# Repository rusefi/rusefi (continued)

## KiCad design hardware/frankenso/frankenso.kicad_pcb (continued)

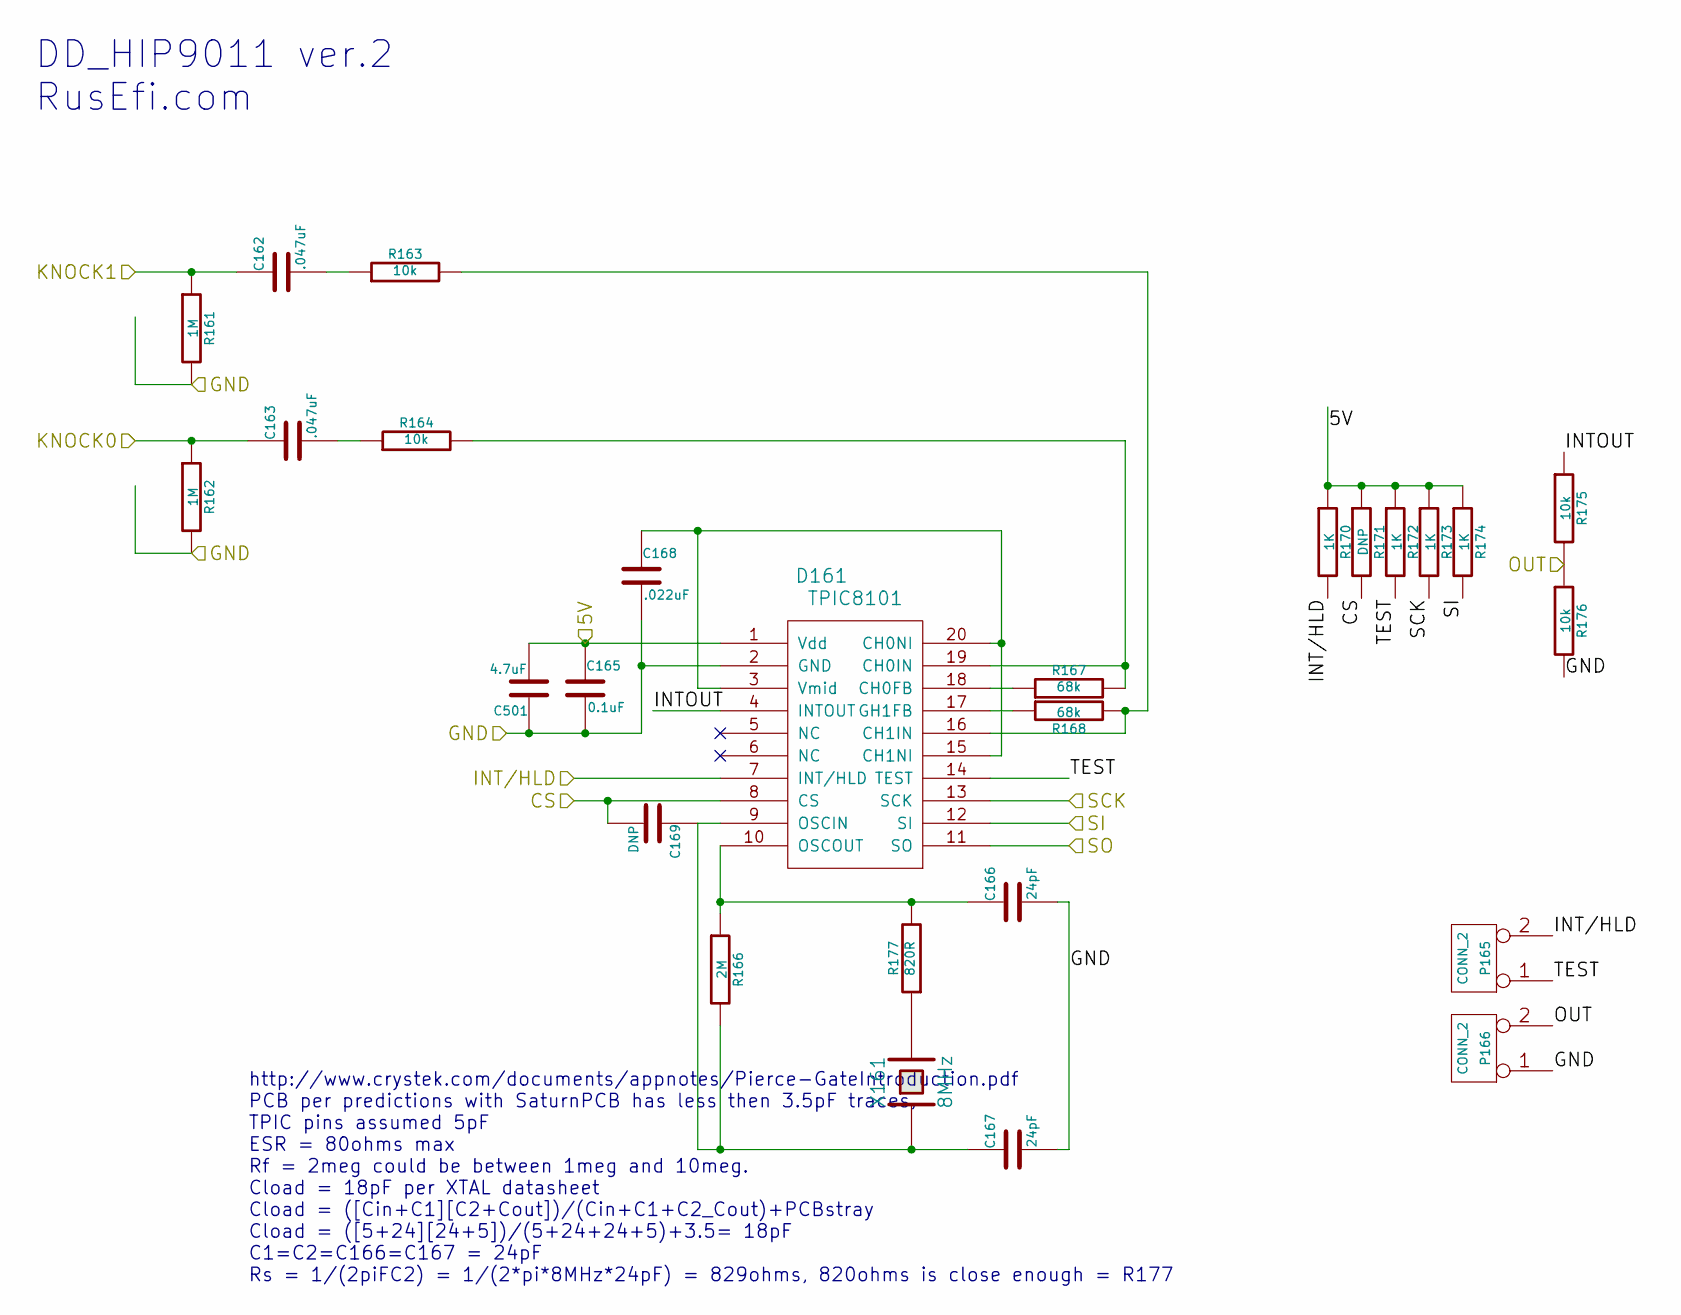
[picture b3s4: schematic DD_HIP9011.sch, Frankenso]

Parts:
C162, C163: .047uF; SM0805
C165: 0.1uF; SM0805
C166, C167: 24pF; SM0805
C168: .022uF; SM0805
C169: DNP; SM0805
C501: 4.7uF; SM0805
D161: TPIC8101; SO20L
P165, P166: CONN_2; PIN_ARRAY_2X1
R161, R162: 1M; SM0805
R163, R164, R175, R176: 10k; SM0805
R166: 2M; SM0805
R167, R168: 68k; SM0805
R170, R172, R173, R174: 1K; SM0805
R171: DNP; SM0805
R177: 820R; SM0805
X161: 8MHz; Q_49U3HMS

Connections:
/DD_HIP9011/5V: C165.1, C501.2, D161.1 (Vdd), R170.1, R171.1, R172.1, R173.1, R174.1; also elsewhere on the board
/DD_HIP9011/CS: C169.2, D161.8 (CS), R171.2; also elsewhere on the board
/DD_HIP9011/INT/HLD: D161.7 (INT/HLD), P165.2 (PM), R170.2; also elsewhere on the board
/DD_HIP9011/INTOUT: D161.4 (INTOUT), R175.1
/DD_HIP9011/KNOCK0: C163.1, R162.1; also elsewhere on the board
/DD_HIP9011/KNOCK1: C162.1, R161.1; also elsewhere on the board
/DD_HIP9011/OUT: P166.2 (PM), R175.2, R176.1; also elsewhere on the board
/DD_HIP9011/TEST: D161.14 (TEST), P165.1, R172.2
/stm32f407_board/PB13: D161.13 (SCK), R173.2; also elsewhere on the board
/stm32f407_board/PB14: D161.11 (SO); also elsewhere on the board
/stm32f407_board/PB15: D161.12 (SI), R174.2; also elsewhere on the board
GND: C165.2, C166.2, C167.2, C168.2, C501.1, D161.2 (GND), P166.1, R161.2, R162.2, R176.2; also elsewhere on the board
unnamed: C168.1, D161.3 (Vmid), D161.15 (CH1NI), D161.20 (CH0NI)
unnamed: C167.1, C169.1, D161.9 (OSCIN), R166.2, X161.1
unnamed: R177.1, X161.2
unnamed: C162.2, R163.1
unnamed: C166.1, D161.10 (OSCOUT), R166.1, R177.2
unnamed: C163.2, R164.1
unnamed: D161.17 (GH1FB), R168.1
unnamed: D161.19 (CH0IN), R164.2, R167.2
unnamed: D161.16 (CH1IN), R163.2, R168.2
unnamed: D161.18 (CH0FB), R167.1

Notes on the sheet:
DD_HIP9011 ver.2 RusEfi.com
http://www.crystek.com/documents/appnotes/Pierce-GateIntroduction.pdf PCB per predictions with SaturnPCB has less then 3.5pF traces, TPIC pins assumed 5pF ESR = 80ohms max Rf = 2meg could be between 1meg and 10meg. Cload = 18pF per XTAL datasheet Cload = ([Cin+C1][C2+Cout])/(Cin+C1+C2_Cout)+PCBstra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

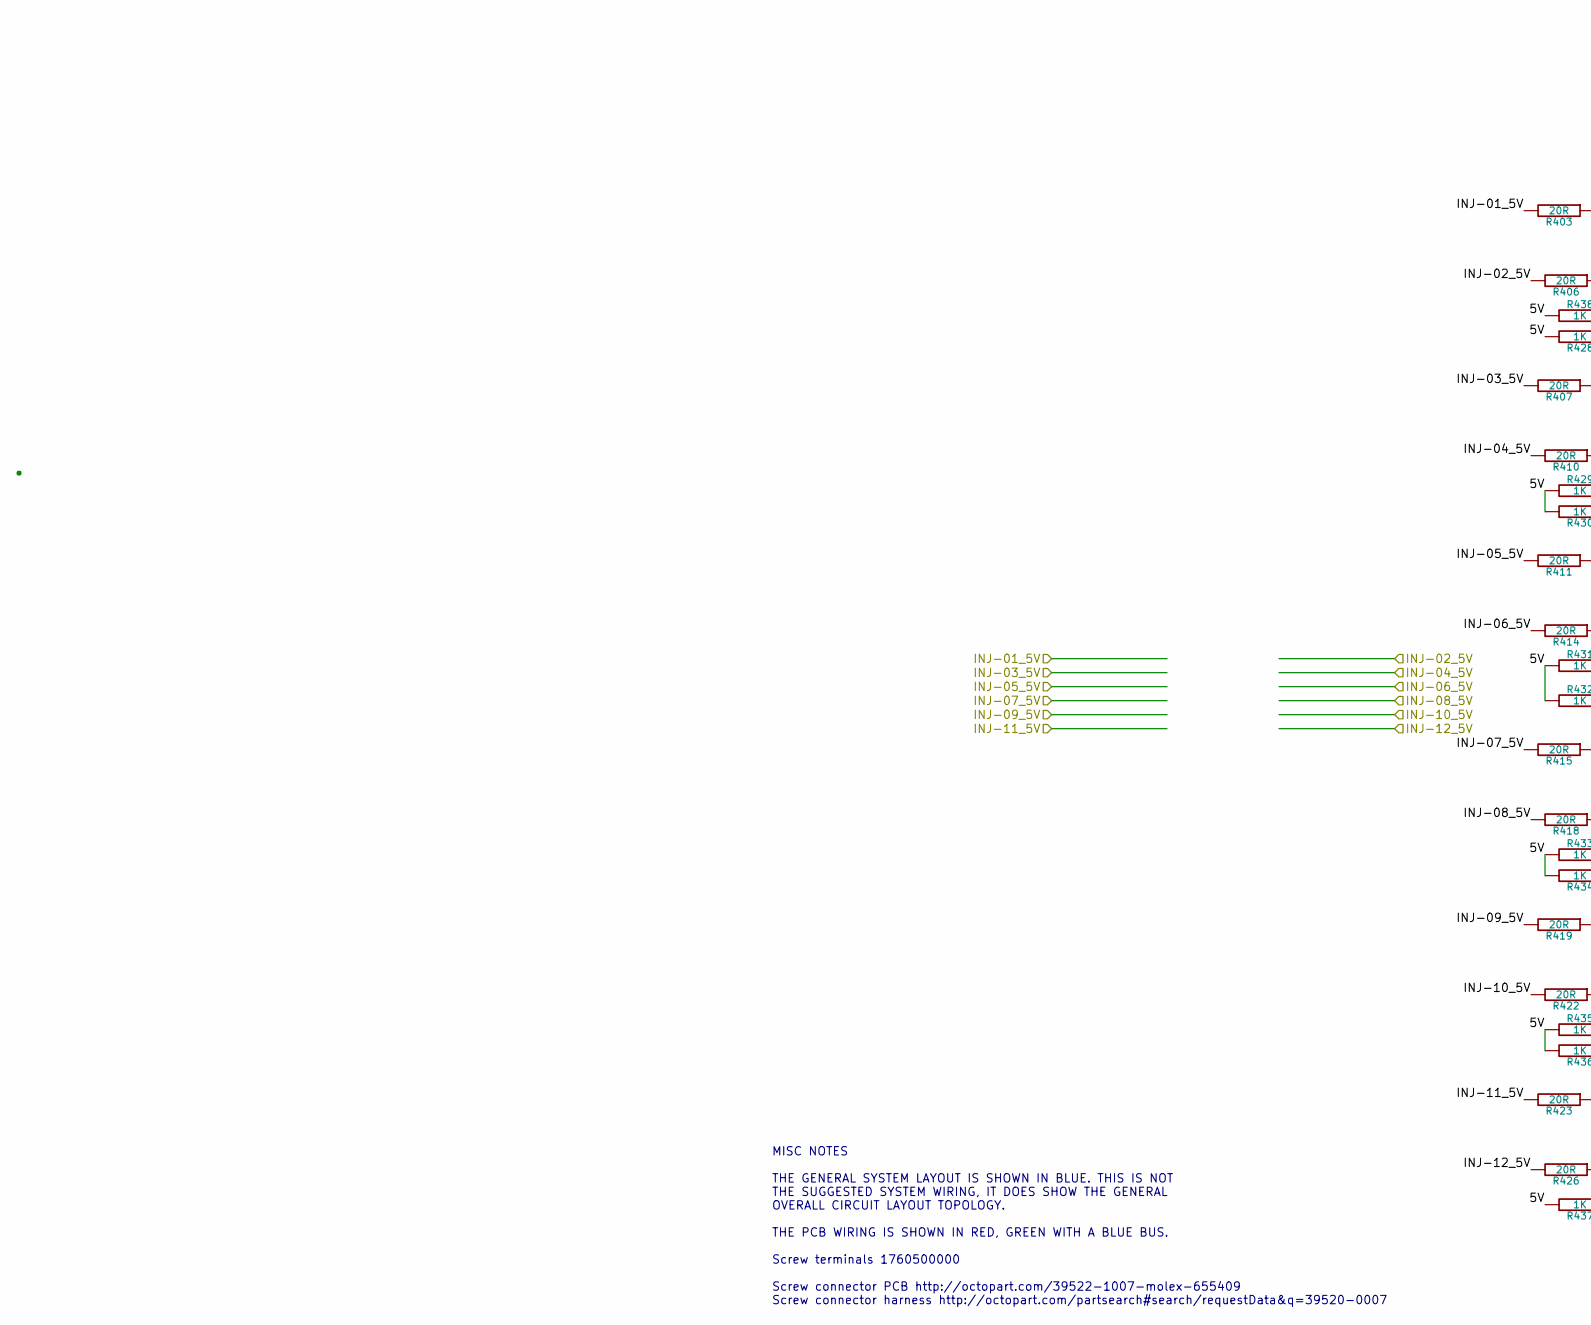
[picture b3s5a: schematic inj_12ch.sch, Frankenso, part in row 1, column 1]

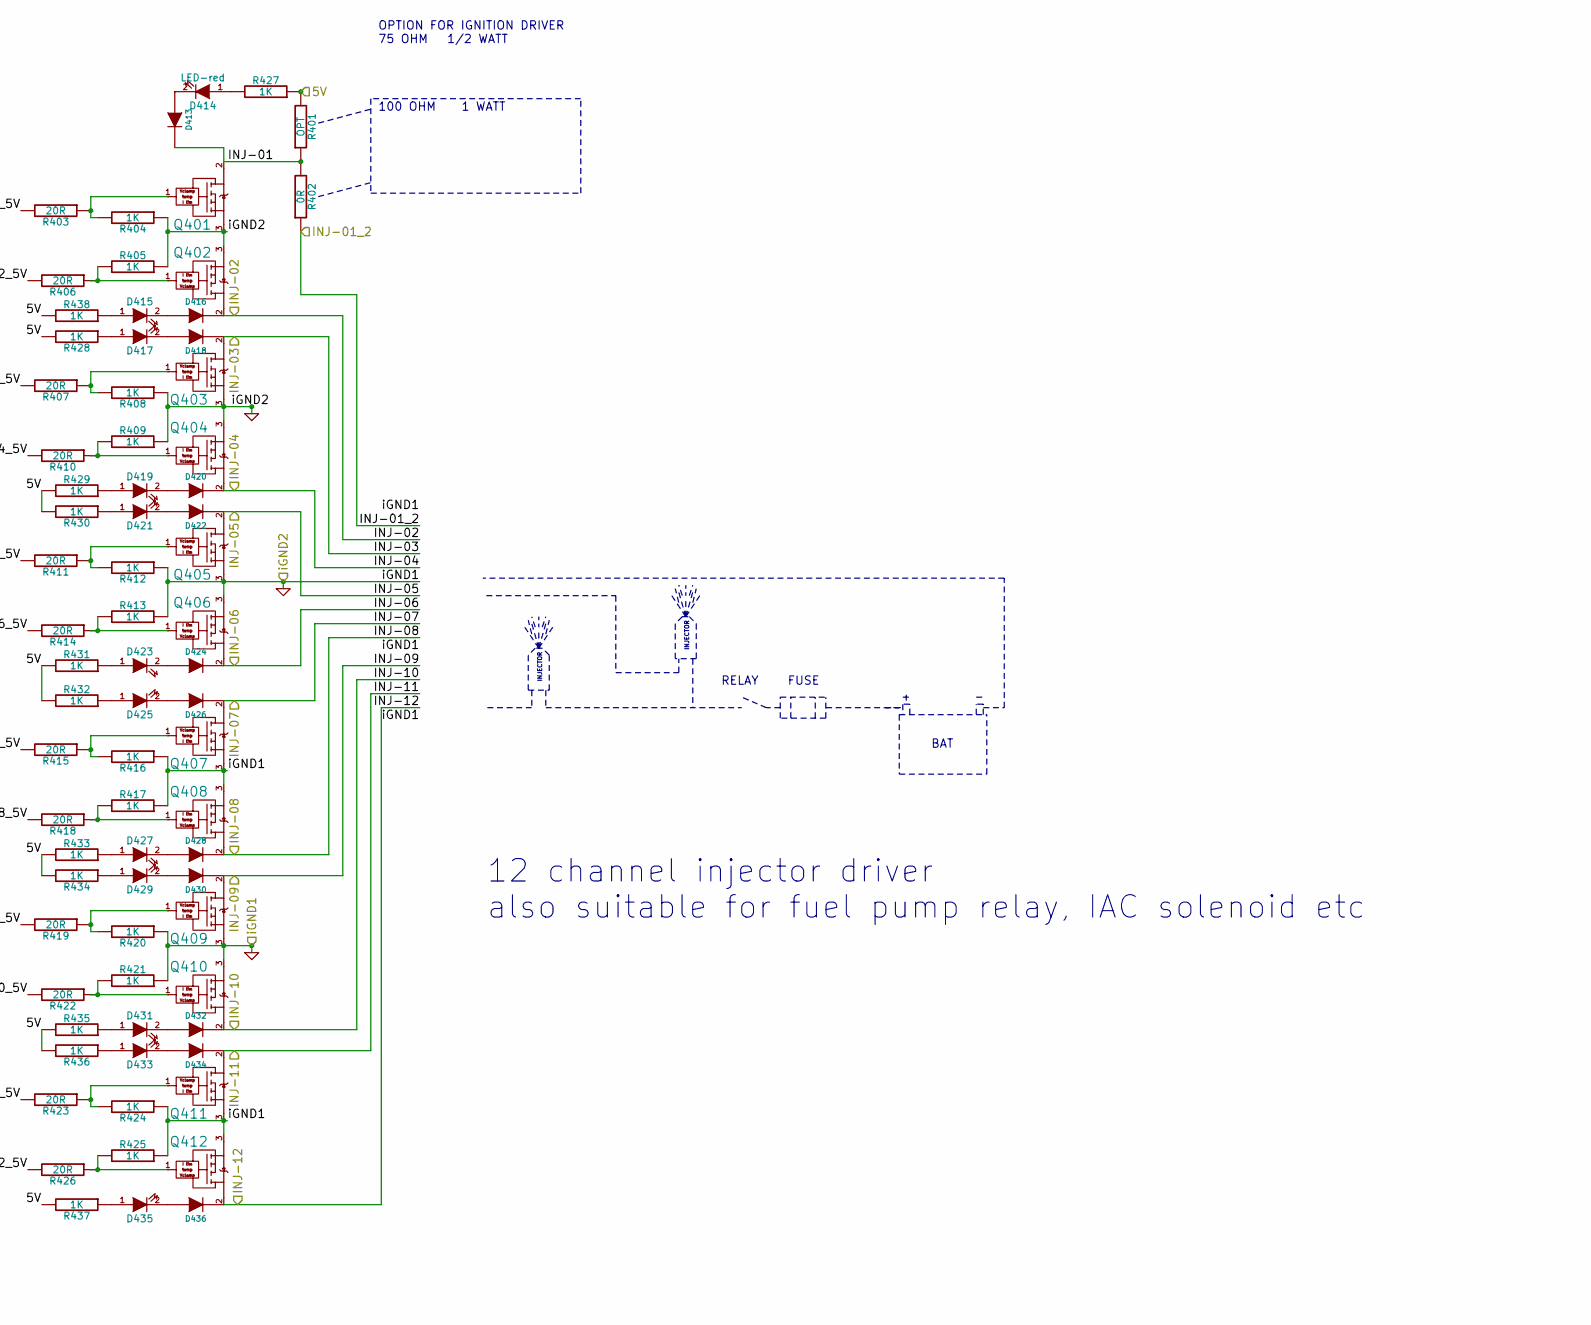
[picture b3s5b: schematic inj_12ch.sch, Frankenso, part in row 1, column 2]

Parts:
D413, D416, D418, D420, D422, D424, D426, D428, D430, D432, D434, D436: DIODE; SOD-123
D414, D415, D417, D419, D421, D423, D425, D427, D429, D431, D433, D435: LED-red; LED-0805_A
Q401, Q402, Q403, Q404, Q405, Q406, Q407, Q408, Q409, Q410, Q411, Q412: OVP_DRIVER; SO8E_ST
R401: OPT; SIL-2
R402: 0R; SIL-2
R403, R406, R407, R410, R411, R414, R415, R418, R419, R422, R423, R426: 20R; SM0805
R404, R405, R408, R409, R412, R413, R416, R417, R420, R421, R424, R425, R427, R428, R429, R430, R431, R432, R433, R434, R435, R436, R437, R438: 1K; SM0805

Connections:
/DD_HIP9011/5V: R401.2, R427.1, R428.2, R429.2, R430.2, R431.2, R432.2, R433.2, R434.2, R435.2, R436.2, R437.2, R438.2; also elsewhere on the board
/inj_12ch/INJ-01: D413.2 (K), Q401.2 (C), R401.1, R402.2
/inj_12ch/INJ-01_2: R402.1; also elsewhere on the board
/inj_12ch/INJ-01_5V: R403.2; also elsewhere on the board
/inj_12ch/INJ-02: D416.2 (K), Q402.2 (C); also elsewhere on the board
/inj_12ch/INJ-02_5V: R406.2; also elsewhere on the board
/inj_12ch/INJ-03: D418.2 (K), Q403.2 (C); also elsewhere on the board
/inj_12ch/INJ-03_5V: R407.2; also elsewhere on the board
/inj_12ch/INJ-04: D420.2 (K), Q404.2 (C); also elsewhere on the board
/inj_12ch/INJ-04_5V: R410.2; also elsewhere on the board
/inj_12ch/INJ-05: D422.2 (K), Q405.2 (C); also elsewhere on the board
/inj_12ch/INJ-05_5V: R411.2; also elsewhere on the board
/inj_12ch/INJ-06: D424.2 (K), Q406.2 (C); also elsewhere on the board
/inj_12ch/INJ-06_5V: R414.2; also elsewhere on the board
/inj_12ch/INJ-07: D426.2 (K), Q407.2 (C); also elsewhere on the board
/inj_12ch/INJ-07_5V: R415.2; also elsewhere on the board
/inj_12ch/INJ-08: D428.2 (K), Q408.2 (C); also elsewhere on the board
/inj_12ch/INJ-08_5V: R418.2; also elsewhere on the board
/inj_12ch/INJ-09: D430.2 (K), Q409.2 (C); also elsewhere on the board
/inj_12ch/INJ-09_5V: R419.2; also elsewhere on the board
/inj_12ch/INJ-10: D432.2 (K), Q410.2 (C); also elsewhere on the board
/inj_12ch/INJ-10_5V: R422.2; also elsewhere on the board
/inj_12ch/INJ-11: D434.2 (K), Q411.2 (C); also elsewhere on the board
/inj_12ch/INJ-11_5V: R423.2; also elsewhere on the board
/inj_12ch/INJ-12: D436.2 (K), Q412.2 (C); also elsewhere on the board
/inj_12ch/INJ-12_5V: R426.2; also elsewhere on the board
GND: Q401.3 (E), Q402.3 (E), Q403.3 (E), Q404.3 (E), Q405.3 (E), Q406.3 (E), Q407.3 (E), Q408.3 (E), Q409.3 (E), Q410.3 (E), Q411.3 (E), Q412.3 (E), R404.1, R405.1, R408.1, R409.1, R412.1, R413.1, R416.1, R417.1, R420.1, R421.1, R424.1, R425.1; also elsewhere on the board
unnamed: Q401.1 (G), R403.1, R404.2
unnamed: Q403.1 (G), R407.1, R408.2
unnamed: Q406.1 (G), R413.2, R414.1
unnamed: Q412.1 (G), R425.2, R426.1
unnamed: Q410.1 (G), R421.2, R422.1
unnamed: Q408.1 (G), R417.2, R418.1
unnamed: D413.1 (A), D414.2 (K)
unnamed: D414.1 (A), R427.2
unnamed: Q402.1 (G), R405.2, R406.1
unnamed: Q404.1 (G), R409.2, R410.1
unnamed: Q405.1 (G), R411.1, R412.2
unnamed: Q407.1 (G), R415.1, R416.2
unnamed: Q409.1 (G), R419.1, R420.2
unnamed: Q411.1 (G), R423.1, R424.2
unnamed: D417.1 (A), R428.1
unnamed: D417.2 (K), D418.1 (A)
unnamed: D419.2 (K), D420.1 (A)
unnamed: D419.1 (A), R429.1
unnamed: D421.2 (K), D422.1 (A)
unnamed: D421.1 (A), R430.1
unnamed: D423.2 (K), D424.1 (A)
unnamed: D423.1 (A), R431.1
unnamed: D415.2 (K), D416.1 (A)
unnamed: D415.1 (A), R438.1
unnamed: D433.1 (A), R436.1
unnamed: D431.2 (K), D432.1 (A)
unnamed: D431.1 (A), R435.1
unnamed: D433.2 (K), D434.1 (A)
unnamed: D435.2 (K), D436.1 (A)
unnamed: D435.1 (A), R437.1
unnamed: D427.1 (A), R433.1
unnamed: D425.2 (K), D426.1 (A)
unnamed: D425.1 (A), R432.1
unnamed: D427.2 (K), D428.1 (A)
unnamed: D429.2 (K), D430.1 (A)
unnamed: D429.1 (A), R434.1

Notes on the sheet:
INJECTOR
RELAY
MISC NOTES THE GENERAL SYSTEM LAYOUT IS SHOWN IN BLUE. THIS IS NOT THE SUGGESTED SYSTEM WIRING, IT DOES SHOW THE GENERAL OVERALL CIRCUIT LAYOUT TOPOLOGY. THE PCB WIRING IS SHOWN IN RED, GREEN WITH A BLUE BUS. Screw terminals 1760500000 Screw connector PCB http://octopart.com/39522-1007-molex-655409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
BAT
FUSE
OPTION FOR IGNITION DRIVER 75 OHM 1/2 WATT 100 OHM 1 WATT
12 channel injector driver also suitable for fuel pump relay, IAC solenoid etc

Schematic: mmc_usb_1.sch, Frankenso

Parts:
C351: 4700pF; SM0805
C352, C353: 47pF; SM0805
C354, C358: 4.7uF; SM0805
C355, C356, C357, C701, C702: 0.1uF; SM0805
D351, D701, D702: LED-grn; LED-0805_A
D703: DOUBLE_SCHOTTKY; sot23
FB701: FILTER; SM0805_jumper
J351: MINI-USB-5P-3400020P1
J352: MINI-USB-5P-3400020P1V; MINI-USB_RCTP_V-T_B
P352: MICRO-SDCARD-CONNECTOR-3300060P1
Q701: MOS_PRO; SOT23
R351: 1M; SM0805
R352, R701, R702, R703: 1k; SM0805
U351: FT232RL; ssop-28
W701: TEST; SM0805_jumper
W702, W703: TEST; SM0805

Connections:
/DD_HIP9011/5V: D703.2 (AK), R701.1, R702.1, W701.1; also elsewhere on the board
/Misc_Vias/3.3V: C357.2, C358.1, P352.4 (Vdd); also elsewhere on the board
/mmc_usb_1/CB2: U351.13 (CBUS2), W702.1
/mmc_usb_1/CB4: U351.12 (CBUS4), W702.2
/mmc_usb_1/CS_SD_MODULE: P352.2 (CS); also elsewhere on the board
/mmc_usb_1/D+: C353.2, J351.3 (D+), J352.3 (D+), U351.15 (USBD+)
/mmc_usb_1/D-: C352.2, J351.2 (D-), J352.2 (D-), U351.16 (USBD-)
/mmc_usb_1/FTVCC: C354.1, C355.2, FB701.2, Q701.2, U351.4 (VCCIO), U351.20 (VCC)
/mmc_usb_1/PWREN#: R703.2, U351.14 (CBUS3)
/mmc_usb_1/RESET: U351.19 (RESET), W703.2
/mmc_usb_1/RI: U351.6 (RI), W703.1
/mmc_usb_1/Vbus: FB701.1, J351.1 (VBUS), J352.1 (VBUS), R352.1
/mmc_usb_1/shield: C351.2, J351.6 (SHIELD), J352.6 (SHIELD), R351.1
/stm32f407_board/PB3: P352.5 (SCLK); also elsewhere on the board
/stm32f407_board/PB5: P352.3 (DI); also elsewhere on the board
/stm32f407_board/PC10: U351.5 (RXD); also elsewhere on the board
/stm32f407_board/PC11: U351.1 (TXD); also elsewhere on the board
/thermocouple1/MISO: P352.7 (DO); also elsewhere on the board
GND: C351.1, C352.1, C353.1, C354.2, C355.1, C356.1, C357.1, C358.2, C702.2, D351.2 (K), J351.5 (GND), J352.5 (GND), P352.6 (Vss/GND), P352.G1 (-), P352.G2 (-), P352.G3 (-), P352.G4 (-), R351.2, U351.7 (GND), U351.18 (GND), U351.21 (GND), U351.25 (AGND), U351.26 (TEST); also elsewhere on the board
unnamed: C356.2, U351.17 (3V3OUT)
unnamed: D701.2 (K), U351.23 (CBUS0)
unnamed: D351.1 (A), R352.2
unnamed: D701.1 (A), R701.2
unnamed: D702.2 (K), U351.22 (CBUS1)
unnamed: C701.1, Q701.1, R703.1
unnamed: D702.1 (A), R702.2
unnamed: C701.2, C702.1, D703.1 (Anode), Q701.3, W701.2

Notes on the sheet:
For right conn
SD card slot USB TTL module
WJ01 IS A BACKUP PLAN. THE VOLTAGE DROP ACROSS D703 MAY BE NOT TOLERABLE, SO WE HAVE A BACK UP PLAN IF WE NEED TO BYPASS THE DIODE WITH A LOWER VOLTAGE DROP

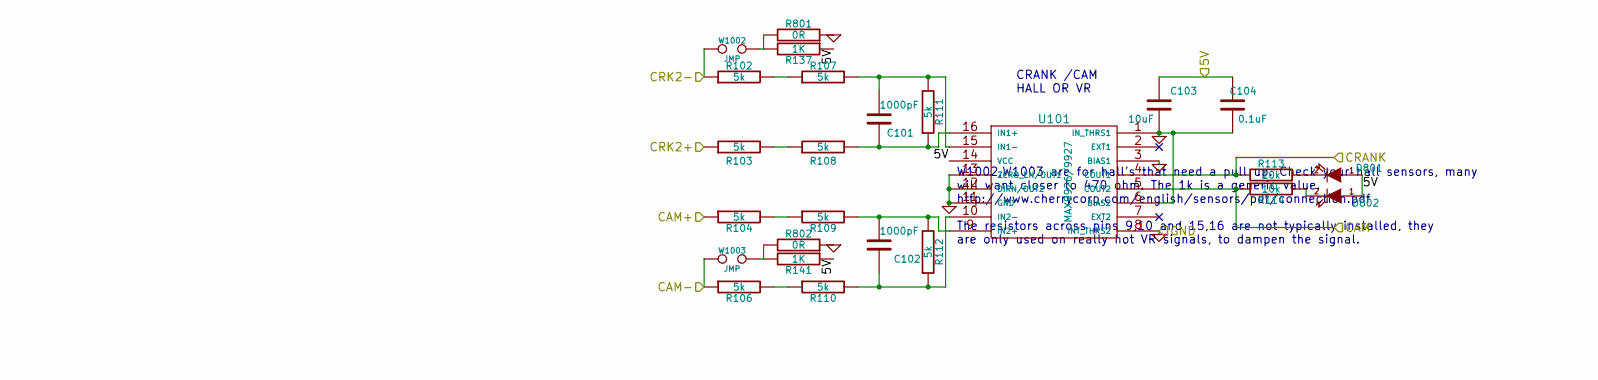
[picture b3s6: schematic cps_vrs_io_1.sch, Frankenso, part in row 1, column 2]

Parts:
C101, C102: 1000pF; SM0805
C103: 10uF; SM0805; tolerance 10%
C104: 0.1uF; SM0805
D801, D802: LED-red; LED-0805_A
R102, R103, R104, R106, R107, R108, R109, R110, R111, R112: 5k; SM0805
R113, R114: 10k; SM0805
R137, R141: 1K; SM0805
R801, R802: 0R; SM0805
U101: MAX9926/9927; maxim-10-QSOP16
W1002, W1003: JMP; SIL-2

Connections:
/DD_HIP9011/5V: C103.2, C104.1, D801.1 (A), D802.1 (A), R137.1, R141.1, U101.14 (VCC); also elsewhere on the board
/Misc_Vias/CAM: R114.1, U101.5 (COUT2); also elsewhere on the board
/Misc_Vias/CRANK: R113.2, U101.4 (COUT1); also elsewhere on the board
/cps_vrs_io_1/CAM+: R104.1; also elsewhere on the board
/cps_vrs_io_1/CAM-: R106.1, W1003.1; also elsewhere on the board
/cps_vrs_io_1/CRK2+: R103.1; also elsewhere on the board
/cps_vrs_io_1/CRK2-: R102.1, W1002.1; also elsewhere on the board
GND: C103.1, C104.2, R801.1, R802.1, U101.1 (IN_THRS1), U101.3 (BIAS1), U101.6 (BIAS2), U101.8 (INT_THRS2), U101.11 (GND), U101.12 (DIRN/OUT2), U101.13 (ZERO_EN/OUT1); also elsewhere on the board
unnamed: R102.2, R107.1
unnamed: R104.2, R109.1
unnamed: R106.2, R110.1
unnamed: R103.2, R108.1
unnamed: R141.2, R802.2, W1003.2
unnamed: R137.2, R801.2, W1002.2
unnamed: D802.2 (K), R114.2
unnamed: D801.2 (K), R113.1
unnamed: C102.1, R110.2, R112.1, U101.10 (IN2-)
unnamed: C101.2, R107.2, R111.2, U101.15 (IN1-)
unnamed: C101.1, R108.2, R111.1, U101.16 (IN1+)
unnamed: C102.2, R109.2, R112.2, U101.9 (IN2+)

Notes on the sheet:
W1002,W1003 are for hall's that need a pull up. Check your hall sensors, many will want closer to 470 ohm. The 1k is a generic value. http://www.cherrycorp.com/english/sensors/pdf/connection.pdf The resistors across pins 9,10 and 15,16 are not typically installed, they are only used on really hot V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
CRANK /CAM HALL OR VR

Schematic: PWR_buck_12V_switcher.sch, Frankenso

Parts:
C1001: 330uF 35V; SMDSVP10
C1002, C1003: 220uF 16V; SM2512
D1001: ZENERSMALL; SM1206
D1002, D1003: TVS; D3
D1004: SCHDPAK; DPAK2
D1005: LED-grn; LED-0805
D1006: DIODESCH; D4
F1001: 3.5A; SIL-2
L1001, L1002: 38uH; SM100uH
P901, P902, P1002: CONN_1; SIL-1
Q1001: MOS_PRO; SOT23
R1001, R1002: 1k; SM0805
U1001: LM2596; DPAK5

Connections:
/PWR_buck_12V_switcher/5V-REG: C1003.1, L1002.2; also elsewhere on the board
/PWR_buck_12V_switcher/FB: C1002.1, L1001.2, L1002.1, R1002.1, U1001.4 (FB)
/PWR_buck_12V_switcher/OUT: D1004.2 (K), D1006.2 (K), L1001.1, P1002.1, U1001.2 (OUT)
/PWR_buck_12V_switcher/VBAT: C1001.1, D1001.2, D1002.2 (K), D1003.2 (K), P902.1, Q1001.2, U1001.1 (IN)
/PWR_buck_12V_switcher/Vf: F1001.2, Q1001.3
/hi-lo/12V: F1001.1, P901.1; also elsewhere on the board
GND: C1001.2, C1002.2, C1003.2, D1002.1 (A), D1003.1 (A), D1004.1 (A), D1004.3 (A), D1005.2 (K), D1006.1 (A), R1001.2, U1001.3 (GND), U1001.5 (EN); also elsewhere on the board
unnamed: D1001.1, Q1001.1, R1001.1
unnamed: D1005.1 (A), R1002.2

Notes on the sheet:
ALT DIODE FOR CHINA ASSEMBLER LIMITS OUTPUT TO 2.3A
